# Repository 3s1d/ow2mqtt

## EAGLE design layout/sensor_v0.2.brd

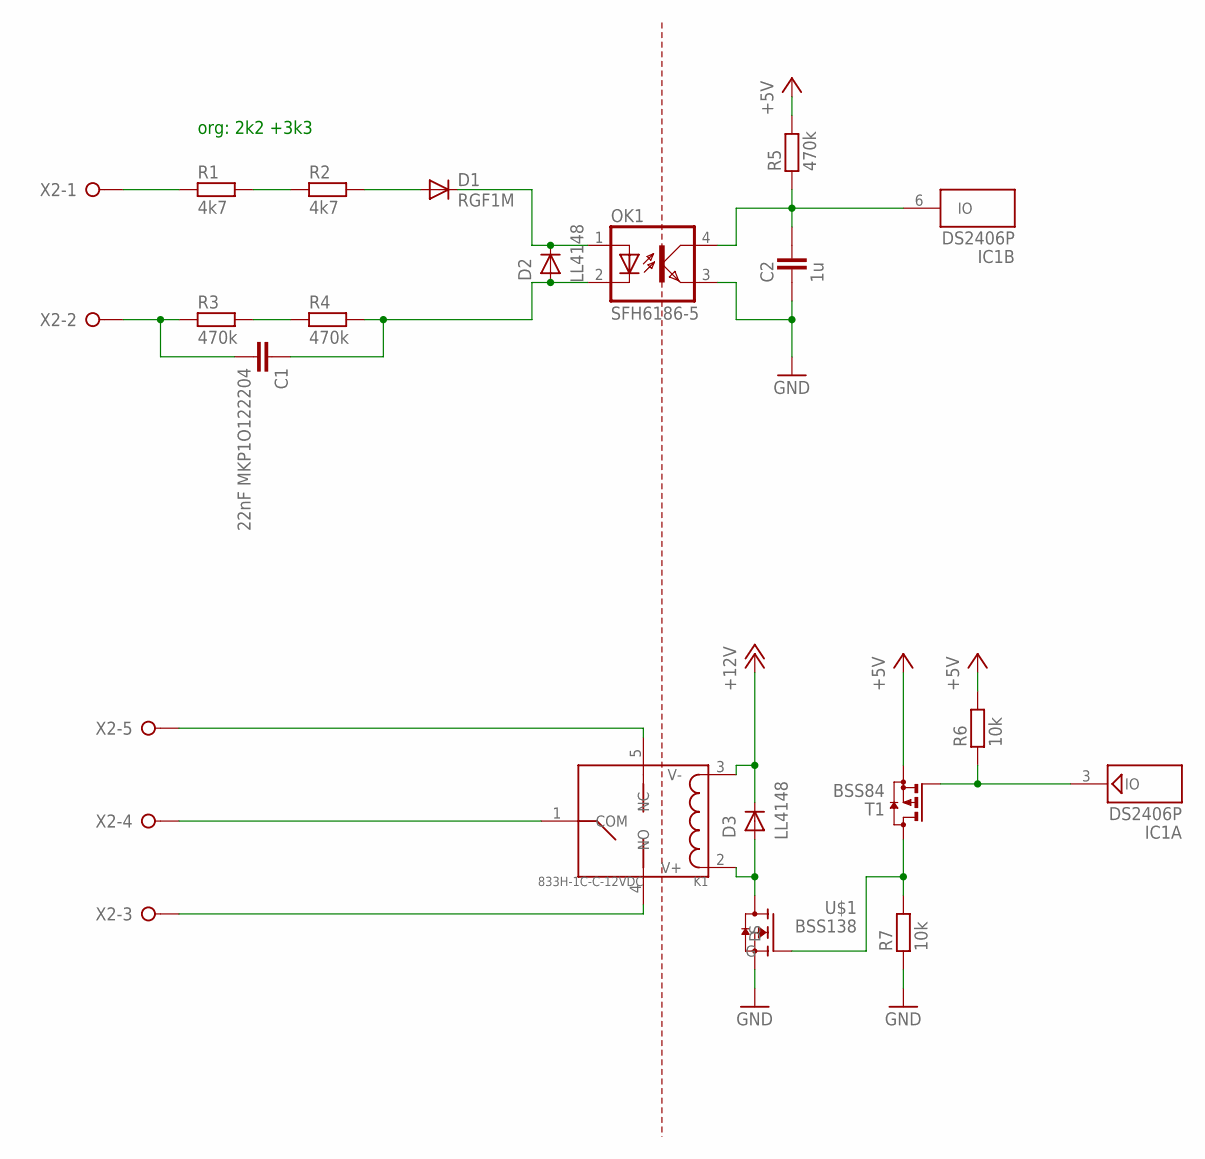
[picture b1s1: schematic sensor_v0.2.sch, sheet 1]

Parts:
C1: 22nF MKP1O122204; C150-064X183
C2: 1u; CAPC1608X92N
D1: RGF1M; DO214BA
D2, D3: LL4148; SOD80C
IC1: DS2406P; TSOC6
K1: 833H-1C-C-12VDC; REY5-19.0X15.0X15.0MM
OK1: SFH6186-5; SMD4
R1, R2: 4k7; RESC6432X70N
R3, R4: 470k; RESC6432X70N
R5: 470k; RESC1005X40AN
R6, R7: 10k; RESC1005X40AN
T1: BSS84; SOT23
U$1: BSS138
X2: W237-05P; W237-5P

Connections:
!EN: IC1.3 (IO), R6.1, T1.1 (G)
!PWR: C2.2, IC1.6 (IO), OK1.4 (COL), R5.1
+5V: R5.2, R6.2, T1.2 (S); also elsewhere on the board
+12V: D3.1 (K), K1.3 (V-); also elsewhere on the board
GND: C2.1, OK1.3 (EMIT), R7.1, U$1.S; also elsewhere on the board
unnamed: R1.1, X2.1
unnamed: R1.2, R2.1
unnamed: R3.2, R4.1
unnamed: C1.2, R3.1, X2.2
unnamed: D1.A, R2.2
unnamed: C1.1, D2.2 (A), OK1.2 (C), R4.2
unnamed: D1.C, D2.1 (K), OK1.1 (A)
unnamed: K1.1 (COM), X2.4
unnamed: K1.5 (NC), X2.5
unnamed: K1.4 (NO), X2.3
unnamed: R7.2, T1.3 (D), U$1.G
unnamed: D3.2 (A), K1.2 (V+), U$1.D

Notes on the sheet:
org: 2k2 +3k3

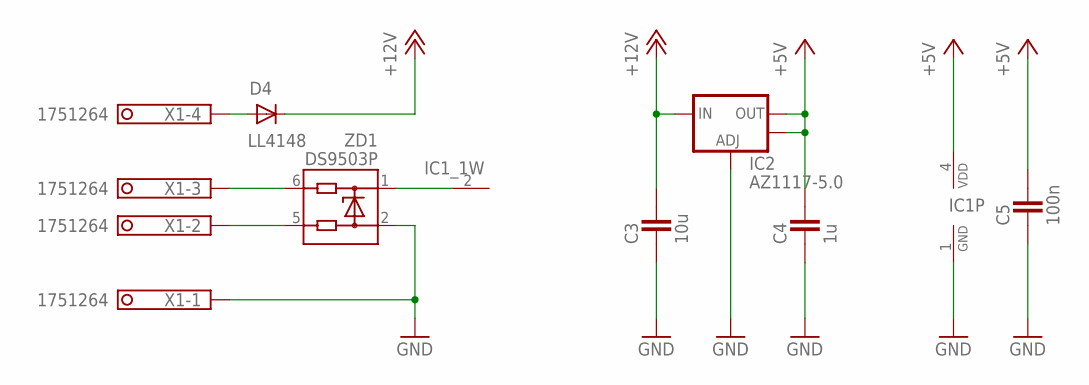
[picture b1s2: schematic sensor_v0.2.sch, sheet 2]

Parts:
C3: 10u; CAPC2012X145AN
C4: 1u; CAPC1608X92N
C5: 100n; CAPC1005X60N
D4: LL4148; SOD80C
IC1: DS2406P; TSOC6
IC2: AZ1117-5.0; SOT223
X1: 1751264
ZD1: DS9503P; TSOC6

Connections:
1W: IC1.2 (1W), ZD1.1
+5V: C4.2, C5.2, IC1.4 (VDD), IC2.2 (OUT), IC2.4 (OUT); also elsewhere on the board
+12V: C3.2, D4.1 (K), IC2.3 (IN); also elsewhere on the board
GND: C3.1, C4.1, C5.1, IC1.1 (GND), IC2.1 (ADJ), X1.1, ZD1.2; also elsewhere on the board
unnamed: X1.2, ZD1.5
unnamed: X1.3, ZD1.6
unnamed: D4.2 (A), X1.4

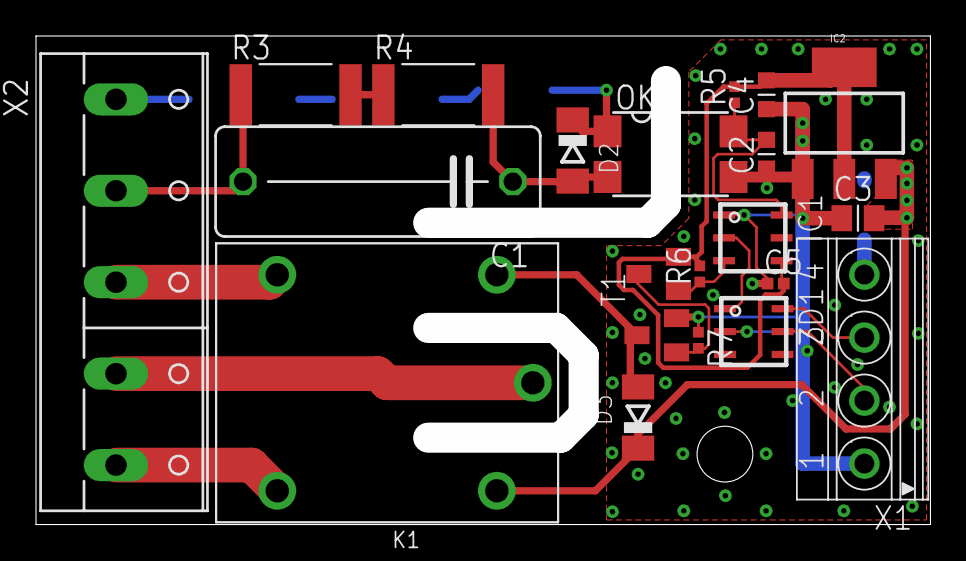
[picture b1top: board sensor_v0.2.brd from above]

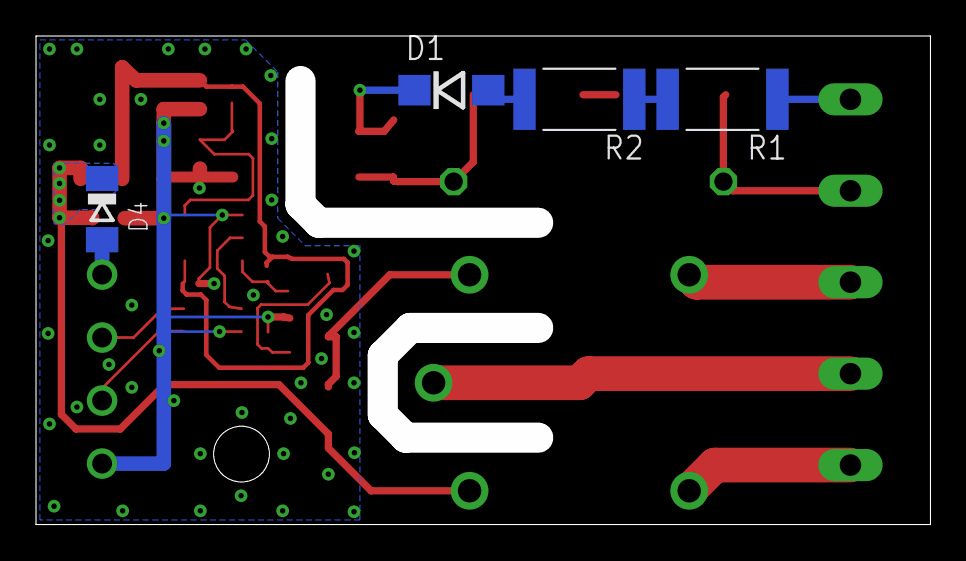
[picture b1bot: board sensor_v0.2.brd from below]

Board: 2 copper layers, 48.0 x 25.5 mm, 25 parts (4 on the bottom side), 21 nets.

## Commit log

2018-06-23 mqtt part working
2018-06-23 sensor board working
2018-06-23 swtich state
2018-06-23 switch working
2018-06-24 added sensor layout
2018-06-24 emulated ram ic readable
2018-06-24 lamp 1w ds2423 emulator
2018-06-25 lamps get broadcasted
2018-06-26 ow command evaluation
2018-07-05 led fade channel/timing based
2018-07-15 added pca9685
2018-11-18 updatged IDs. useCache() blocks for current version??? WAT
2019-04-22 unified
2021-11-30 python3 ready
2023-12-31 pull down fix
2023-12-31 reverted to python2.7 as i have not yet performed the update.... oh well....
2024-01-01 sem testing for cb
2024-01-01 semaphore for ow device

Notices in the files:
parts and their libraries:
SparkFun: Licensing: CC v3.0 Share-Alike You are welcome to use this library for commercial purposes.
